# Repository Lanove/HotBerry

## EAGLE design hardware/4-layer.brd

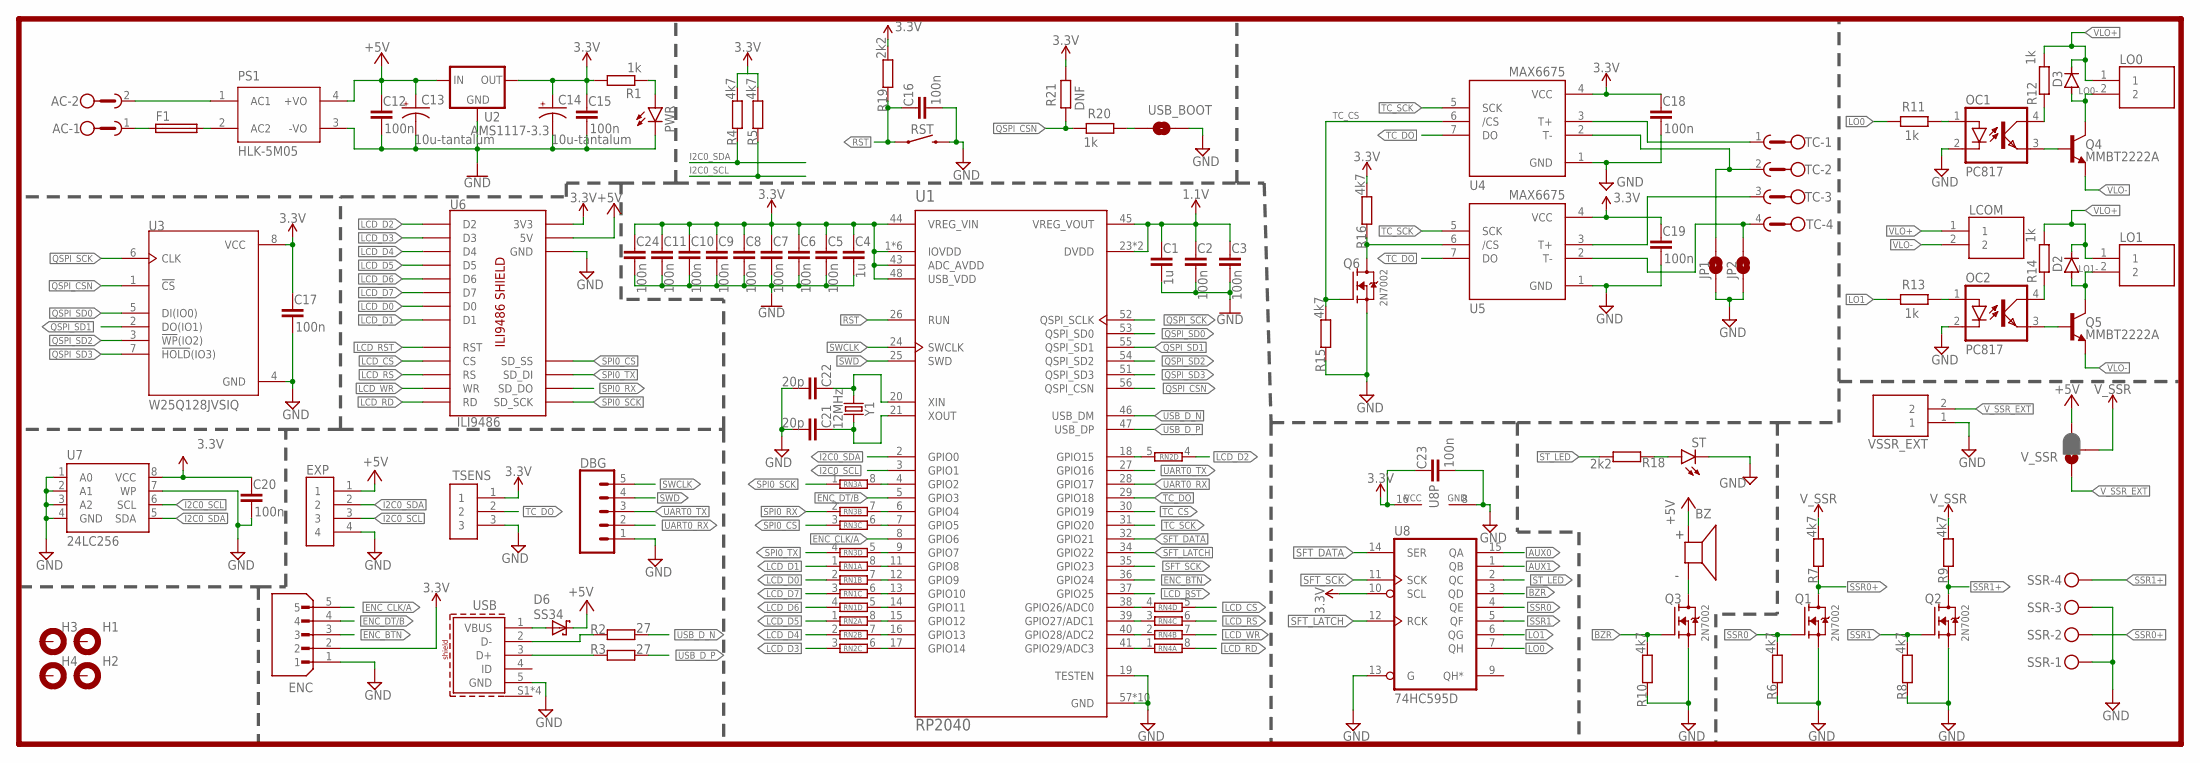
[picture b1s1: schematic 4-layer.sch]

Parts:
AC: GMSTBA2
BZ: AI-1223-TWT-12V-R; XDCR_AI-1223-TWT-12V-R
C1, C4: 1u; C0603K
C2, C3, C5, C6, C7, C8, C9, C10, C11, C12, C15, C16, C17, C18, C19, C20, C23, C24: 100n; C0603K
C13, C14: 10u-tantalum; CT3528
C21, C22: 20p; C0603K
D2, D3: DIODE-DO-214AC; DO-214AC
D6: SS34; DO214
DBG: CONN_05NO_SILK; 1X05_NO_SILK
ENC: B5B-XH-A(LF)(SN); JST_B5B-XH-A(LF)(SN)
EXP: JST-XH-4P; JST_B4B-XH-A(LF)(SN)
F1: FUSEBLANK_5X20MM; FUSE_HOLDER_5X20MM
H1, H2, H3, H4: MOUNT-PAD-ROUND3.2; 3,2-PAD
JP1, JP2: JUMPER-SMT_2_NO_NO-SILK; SMT-JUMPER_2_NO_NO-SILK
LCOM: B2B-XH-A(LF)(SN); JST_B2B-XH-A(LF)(SN)
LO0, LO1: B2B-XH-A(LF)(SN); JST_B2B-XH-A(LF)(SN)
OC1, OC2: PC817; DIL04
PS1: HLK-5M05; CONV_HLK-5M05
PWR: LEDCHIP-LED0805; CHIP-LED0805
Q1, Q2, Q3, Q6: 2N7002; SOT95P240X111-3N
Q4, Q5: MMBT2222A; SOT23-3
R1, R11, R12, R13, R14, R20: 1k; R0603
R2, R3: 27; R0603
R4, R5, R6, R7, R8, R9, R10, R15, R16: 4k7; R0603
R18, R19: 2k2; R0603
R21: DNF; R0603
RN1, RN2, RN3, RN4: 4R-N0402ARV341; 4X0402ARV341
RST: MOMENTARY-SWITCH-SPST-SMD-6.0X3.5MM; TACTILE_SWITCH_SMD_6.0X3.5MM
SSR: MKDSN1,5/4-5,08
ST: LEDCHIP-LED0805; CHIP-LED0805
TC: GMSTBA4
TSENS: B3B-XH-A(LF)(SN); JST_B3B-XH-A(LF)(SN)
U1: RP2040; QFN40P700X700X90-57N
U2: AMS1117-3.3; SOT89R
U3: W25Q128JVSIQ; SOIC127P790X216-8N
U4, U5: MAX6675; SO08
U6: ILI9486; ILI9486-SHIELD
U7: 24LC256; SO08
U8: 74HC595D; SO16
USB: 629105136821
USB_BOOT: JUMPER-SMT_2_NO_SILK; SMT-JUMPER_2_NO_SILK
VSSR_EXT: B2B-XH-A(LF)(SN); JST_B2B-XH-A(LF)(SN)
V_SSR: JUMPER-SMT_3_1-NC_PASTE_SILK; SMT-JUMPER_3_1-NC_PASTE_SILK
Y1: 12MHz; HC49US

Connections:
1.1V: C1.1, C2.1, C3.1, U1.23 (DVDD), U1.45 (VREG_VOUT), U1.50 (DVDD)
3.3V: C4.1, C5.1, C6.1, C7.1, C8.1, C9.1, C10.1, C11.1, C14.+, C15.1, C17.1, C18.1, C19.1, C20.1, C23.1, C24.1, ENC.2, R1.2, R4.1, R5.1, R16.1, R19.1, R21.2, TSENS.1, U1.1 (IOVDD), U1.10 (IOVDD), U1.22 (IOVDD), U1.33 (IOVDD), U1.42 (IOVDD), U1.43 (ADC_AVDD), U1.44 (VREG_VIN), U1.48 (USB_VDD), U1.49 (IOVDD), U2.3 (OUT), U2.4 (OUT), U3.8 (VCC), U4.4 (VCC), U5.4 (VCC), U6.3V3, U7.8 (VCC), U8.10 (SCL), U8.16 (VCC)
+5V: BZ.P (+), C12.1, C13.+, D6.C, EXP.1, PS1.4 (+VO), U2.1 (IN), U6.5V, V_SSR.3
AUX0: U8.15 (QA)
AUX1: U8.1 (QB)
BZR: Q3.1 (G), R10.1, U8.3 (QD)
ENC_BTN: ENC.3, U1.36 (GPIO24)
ENC_CLK/A: ENC.5, U1.8 (GPIO6)
ENC_DT/B: ENC.4, U1.5 (GPIO3)
GND: C1.2, C2.2, C3.2, C4.2, C5.2, C6.2, C7.2, C8.2, C9.2, C10.2, C11.2, C12.2, C13.-, C14.-, C15.2, C16.2, C17.2, C18.2, C19.2, C20.2, C21.2, C22.2, C23.2, C24.2, DBG.1, ENC.1, EXP.4, JP1.1, JP2.1, OC1.2 (C), OC2.2 (C), PS1.3 (-VO), PWR.C, Q1.2 (S), Q2.2 (S), Q3.2 (S), Q6.2 (S), R6.2, R8.2, R10.2, R15.2, RST.2, SSR.1, SSR.3, ST.C, TSENS.3, U1.19 (TESTEN), U1.57 (GND), U1.P$1 (GND), U1.P$2 (GND), U1.P$3 (GND), U1.P$4 (GND), U1.P$5 (GND), U1.P$6 (GND), U1.P$7 (GND), U1.P$8 (GND), U1.P$9 (GND), U2.2 (GND), U3.4 (GND), U4.1 (GND), U5.1 (GND), U6.GND, U6.GND1 (GND), U6.GND2 (GND), U7.1 (A0), U7.2 (A1), U7.3 (A2), U7.4 (GND), U7.7 (WP), U8.8 (GND), U8.13 (G), USB.5 (GND), USB_BOOT.2, VSSR_EXT.1
I2C0_SCL: EXP.3, R5.2, U1.3 (GPIO1), U7.6 (SCL)
I2C0_SDA: EXP.2, R4.2, U1.2 (GPIO0), U7.5 (SDA)
LCD_CS: RN4.5 (2), U6.LCD_CS (CS)
LCD_D0: RN1.2 (1), U6.LCD_D0 (D0)
LCD_D1: RN1.1, U6.LCD_D1 (D1)
LCD_D2: RN2.4 (1), U6.LCD_D2 (D2)
LCD_D3: RN2.3 (1), U6.LCD_D3 (D3)
LCD_D4: RN2.2 (1), U6.LCD_D4 (D4)
LCD_D5: RN2.1, U6.LCD_D5 (D5)
LCD_D6: RN1.4 (1), U6.LCD_D6 (D6)
LCD_D7: RN1.3 (1), U6.LCD_D7 (D7)
LCD_RD: RN4.8 (2), U6.LCD_RD (RD)
LCD_RS: RN4.6 (2), U6.LCD_RS (RS)
LCD_RST: U1.37 (GPIO25), U6.LCD_RST (RST)
LCD_WR: RN4.7 (2), U6.LCD_WR (WR)
LO0: R11.1, U8.7 (QH)
LO0-: D3.A, LO0.2, Q4.3 (C)
LO1: R13.1, U8.6 (QG)
LO1-: D2.A, LO1.2, Q5.3 (C)
unnamed: AC.1, F1.1
unnamed: F1.2, PS1.2 (AC2)
unnamed: AC.2, PS1.1 (AC1)
unnamed: PWR.A, R1.1
unnamed: BZ.N (-), Q3.3 (D)
unnamed: R3.2, USB.3 (D+)
unnamed: R2.2, USB.2 (D-)
unnamed: OC1.1 (A), R11.2
unnamed: OC1.4 (COL), R12.2
unnamed: OC1.3 (EMIT), Q4.1 (B)
unnamed: OC2.1 (A), R13.2
unnamed: OC2.4 (COL), R14.2
unnamed: OC2.3 (EMIT), Q5.1 (B)
unnamed: Q6.3 (D), R16.2, U5.6 (/CS)
unnamed: RN1.6 (2), U1.13 (GPIO10)
unnamed: R20.2, USB_BOOT.1
unnamed: RN1.7 (2), U1.12 (GPIO9)
unnamed: R18.2, ST.A
unnamed: RN1.8 (2), U1.11 (GPIO8)
unnamed: RN1.5 (2), U1.14 (GPIO11)
unnamed: RN2.8 (2), U1.15 (GPIO12)
unnamed: RN2.7 (2), U1.16 (GPIO13)
unnamed: RN2.6 (2), U1.17 (GPIO14)
unnamed: D6.A, USB.1 (VBUS)
unnamed: RN2.5 (2), U1.18 (GPIO15)
unnamed: RN3.8 (2), U1.4 (GPIO2)
unnamed: RN3.7 (2), U1.6 (GPIO4)
unnamed: RN3.6 (2), U1.7 (GPIO5)
unnamed: RN3.5 (2), U1.9 (GPIO7)
unnamed: RN4.4 (1), U1.38 (GPIO26/ADC0)
unnamed: RN4.3 (1), U1.39 (GPIO27/ADC1)
unnamed: RN4.2 (1), U1.40 (GPIO28/ADC2)
unnamed: RN4.1, U1.41 (GPIO29/ADC3)
unnamed: JP2.2, TC.4, U5.2 (T-)
unnamed: JP1.2, TC.2, U4.2 (T-)
QSPI_CSN: R20.1, R21.1, U1.56 (QSPI_CSN), U3.1 (!CS)
QSPI_SCK: U1.52 (QSPI_SCLK), U3.6 (CLK)
QSPI_SD0: U1.53 (QSPI_SD0), U3.5 (DI(IO0))
QSPI_SD1: U1.55 (QSPI_SD1), U3.2 (DO(IO1))
QSPI_SD2: U1.54 (QSPI_SD2), U3.3 (!WP!(IO2))
QSPI_SD3: U1.51 (QSPI_SD3), U3.7 (!HOLD!(IO3))
RST: C16.1, R19.2, RST.1, U1.26 (RUN)
SFT_DATA: U1.32 (GPIO21), U8.14 (SER)
SFT_LATCH: U1.34 (GPIO22), U8.12 (RCK)
SFT_SCK: U1.35 (GPIO23), U8.11 (SCK)
SPI0_CS: RN3.3 (1), U6.SD_SS
SPI0_RX: RN3.2 (1), U6.SD_DO
SPI0_SCK: RN3.1, U6.SD_SCK
SPI0_TX: RN3.4 (1), U6.SD_DI
SSR0: Q1.1 (G), R6.1, U8.4 (QE)
SSR0+: Q1.3 (D), R7.2, SSR.2
SSR1: Q2.1 (G), R8.1, U8.5 (QF)
SSR1+: Q2.3 (D), R9.2, SSR.4
ST_LED: R18.1, U8.2 (QC)
SWCLK: DBG.5, U1.24 (SWCLK)
SWD: DBG.4, U1.25 (SWD)
TC+0: TC.1, U4.3 (T+)
TC+1: TC.3, U5.3 (T+)
TC_CS: Q6.1 (G), R15.1, U1.30 (GPIO19), U4.6 (/CS)
TC_DO: TSENS.2, U1.29 (GPIO18), U4.7 (DO), U5.7 (DO)
TC_SCK: U1.31 (GPIO20), U4.5 (SCK), U5.5 (SCK)
UART0_RX: DBG.2, U1.28 (GPIO17)
UART0_TX: DBG.3, U1.27 (GPIO16)
USB_D_N: R2.1, U1.46 (USB_DM)
USB_D_P: R3.1, U1.47 (USB_DP)
VLO+: D2.C, D3.C, LCOM.1, LO0.1, LO1.1, R12.1, R14.1
VLO-: LCOM.2, Q4.2 (E), Q5.2 (E)
V_SSR: R7.1, R9.1, V_SSR.2
V_SSR_EXT: VSSR_EXT.2, V_SSR.1
XIN: C22.1, U1.20 (XIN), Y1.2
XOUT: C21.1, U1.21 (XOUT), Y1.1

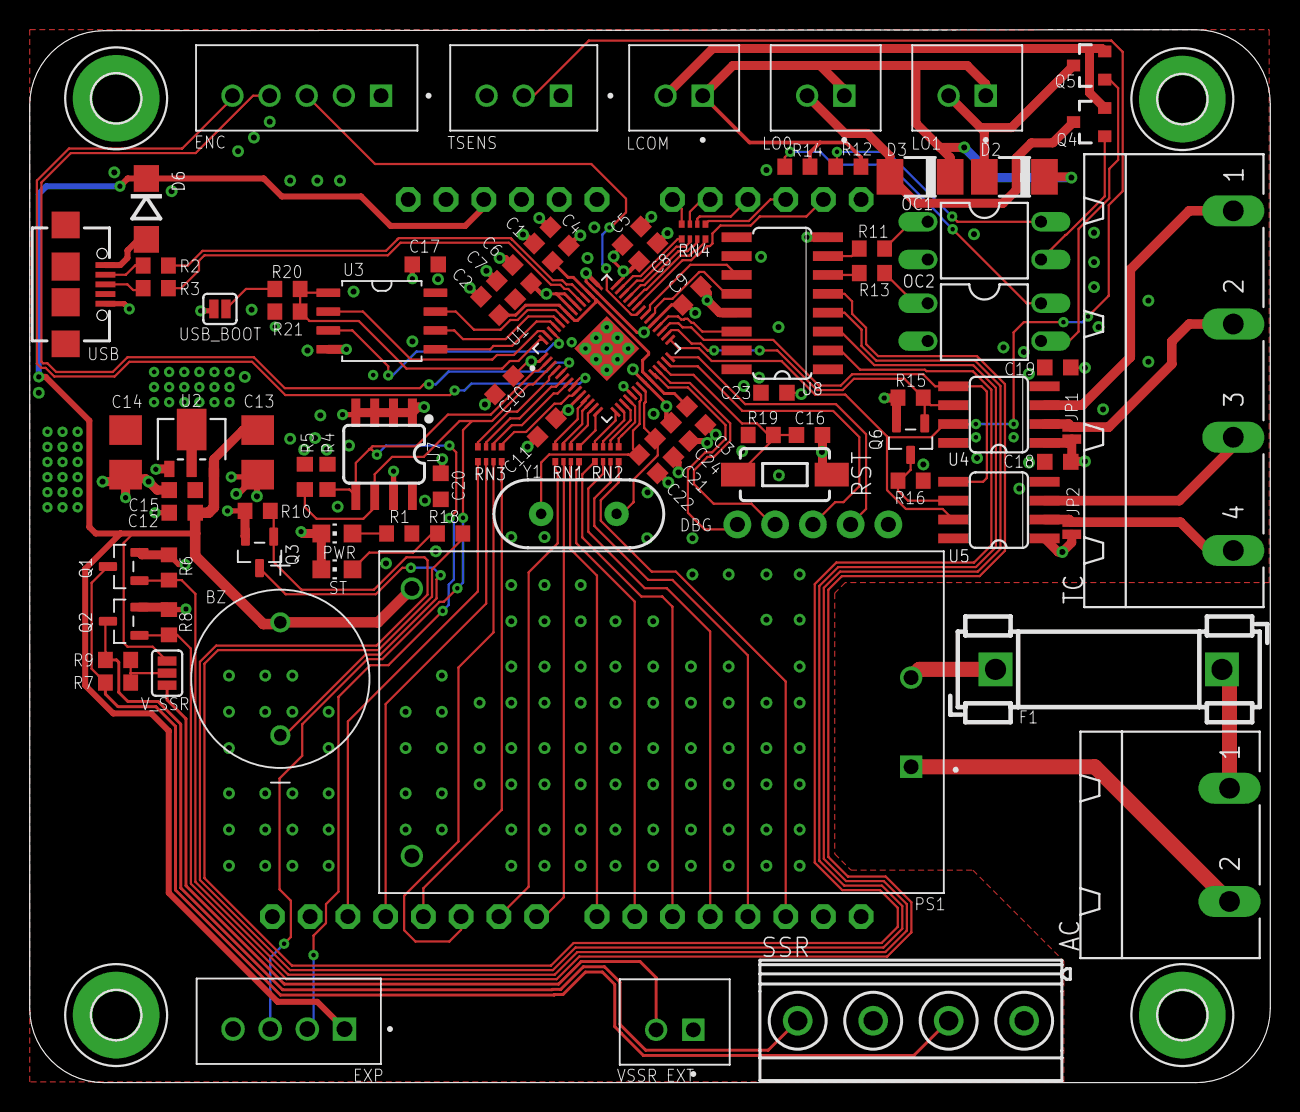
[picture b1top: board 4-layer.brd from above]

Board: 4 copper layers, 83.5 x 70.9 mm, 94 parts (1 on the bottom side), 98 nets.

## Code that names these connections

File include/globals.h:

#ifndef _GLOBALS_H
#define _GLOBALS_H
#include "pico/stdlib.h"
#include <stdio.h>

enum IO
{
    SD_CS = 5,
    SD_RX = 4,
    SD_SCK = 2,
    SD_TX = 7,

    TFT_D0 = 8,
    TFT_D1 = 9,
    TFT_D2 = 10,
    TFT_D3 = 11,
    TFT_D4 = 12,
    TFT_D5 = 13,
    TFT_D6 = 14,
    TFT_D7 = 15,

    TFT_CS = 26, // Also ADC0
    TFT_RS = 27, // Also ADC1
    TFT_WR = 28, // Also ADC2
    TFT_RD = 29, // Also ADC3
    TFT_RST = 25,

    TOUCH_XP = TFT_RD, // ADC channel 3 (TFT_RD)
    TOUCH_YP = SD_TX,
    TOUCH_XM = SD_CS,
    TOUCH_YM = TFT_CS, // ADC channel 0 (TFT_CS)
    TOUCH_YM_ADC_CHANNEL = 0,
    TOUCH_XP_ADC_CHANNEL = 3,

    THERM_DATA = 18,
    THERM_CS = 19,
    THERM_SCK = 20,
    SFT_DATA = 21,
    SFT_LATCH = 22,
    SFT_CLOCK = 23,
    I2C0_SDA = 0,
    I2C0_SCL = 1,
    ENC_A = 6,
    ENC_B = 3,
    ENC_BTN = 24,
    UART0_TX = 16,
    UART0_RX = 17
};

enum SFTO
{
    AUX0 = 0,
    AUX1 = 1,
    ST_LED = 2,
    BUZZER = 3,
    SSR0 = 4,
    SSR1 = 5,
    LO1 = 6,
    LO2 = 7
};

static constexpr uint32_t cpu_freq_mhz = 250;

#endif

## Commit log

2022-06-09 init
2022-06-09 Add hardware files
2022-06-10 TFT Drivers in progress
2022-06-10 TFT Progress
2022-06-11 TFT Driver works, unoptimized uncleaned
2022-06-12 Added touch code, not merged to tft library yet
2022-06-12 Added touch api to tft library Added hotberry board settings to repo
2022-06-14 Added LVGL, PIO WIP
2022-06-14 Added PIO (glitchy display on LVGL)
2022-06-14 Added bodmer init no modification
2022-06-14 Fixed display glitch by removing 22 ohm series resistor on TFT lines
2022-06-14 Added DMA colors transfer
2022-06-14 Added DMA with IRQ
2022-06-14 Changed some init command for better display color and frame rate
2022-06-15 Added Panel Rotations
2022-06-15 Partially refactored, DMA is broken
2022-06-15 Fixed DMA setRotation now uses PIO operation (can be called after init)
2022-06-15 All data and command operation now uses PIO
2022-06-15 ili9486_drivers refactored
2022-06-16 Added MAX6675 driver Added FreeRTOS port (WIP)
2022-06-21 Added lv_drivers and lv_app
2022-07-02 Added more docs Added lv_app
2022-07-04 Added AT24C16 interface library
2022-07-04 Added EEPROM load to lv_app BUG : Choosing profile on profile screen causes crash
2022-07-04 Fixed profile button crash
2022-07-04 Fixed rollpick profile select crash
2022-07-05 Added EEPROM interface to profile and PID memory
2022-07-05 Added top and bottom thermocouple max6675 measurement
2022-07-05 Added 595 lib
2022-07-08 pid failed attempt
2022-07-11 PID brett
2022-07-12 Added FreeRTOS
2022-07-13 Moved LV_APP to FreeRTOS task
2022-07-13 Migrating to FreeRTOS
2022-07-13 Migrating to FreeRTOS...
2022-07-13 Added SSR PWM
2022-07-13 Migrated to FreeRTOS Using Phil's PID controller
2022-07-21 Changed PID constants datatype to double Implemented SSR PWM, the PWM value is sent via queue Implemented PID
2022-07-26 Added comments
2022-07-26 Reverted overclock code
2022-08-02 Added pics

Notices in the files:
parts and their libraries:
Wurth_Connectors_WR-USB: Copyright: Würth Elektronik
SparkFun-Clocks: Licensing: Creative Commons ShareAlike 4.0 International - https://creativecommons.org/licenses/by-sa/4.0
